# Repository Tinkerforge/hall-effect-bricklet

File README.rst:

Hall Effect Bricklet
====================

This repository contains the firmware source code and the hardware design
files. The documentation generator configs can be found at
https://github.com/Tinkerforge/generators

Repository Content
------------------

software/:
 * examples/: Examples for all supported languages
 * build/: Compiled files
 * src/: Source code of firmware
 * Makefile: Makefile to build project

hardware/:
 * Contains KiCad project files and additionally schematics as PDF

datasheets/:
 * Contains datasheets for sensors and complex ICs that are used

Hardware
--------

The hardware is designed with the open source EDA Suite KiCad
(http://www.kicad.org). Before you are able to open the files,
you have to install the Tinkerforge kicad-libraries
(https://github.com/Tinkerforge/kicad-libraries). You can either clone
them directly in hardware/ or clone them in a separate folder and
symlink them into hardware/
(ln -s kicad_path/kicad-libraries project_path/hardware). After that you
can open the .pro file in hardware/ with KiCad and from there view and
modify the schematics and the PCB layout.

Software
--------

If you want to do your own Brick/Bricklet firmware development we highly
recommend that you use our build environment setup script and read the
tutorial (https://www.tinkerforge.com/en/doc/Tutorials/Tutorial_Build_Environment/Tutorial.html).

To compile the C code we recommend you to install the newest GNU Arm Embedded
Toolchain (https://launchpad.net/gcc-arm-embedded/+download).
You also need to install bricklib (https://github.com/Tinkerforge/bricklib)
and brickletlib (https://github.com/Tinkerforge/brickletlib).

You can either clone it directly in software/src/ or clone it in a
separate folder and symlink it into software/src/
(ln -s bricklib_path/bricklib project_path/software/src/ and
ln -s brickletlib_path/brickletlib project_path/software/src/).
Finally make sure to have CMake installed
(http://www.cmake.org/cmake/resources/software.html).

After that you can build the firmware by invoking make in software/.
The firmware (.bin) can then be found in software/build/ and uploaded
with brickv (click button "Flashing" on start screen).

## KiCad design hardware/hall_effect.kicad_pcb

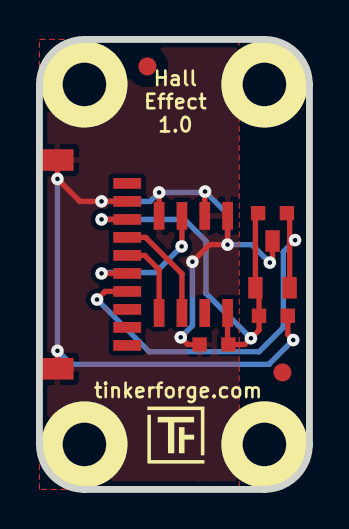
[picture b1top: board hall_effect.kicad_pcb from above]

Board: 2 copper layers, 15.0 x 25.0 mm, 14 parts (0 on the bottom side), 6 nets.

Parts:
C1, C2: 100nF; C0603
Fiducial_Mark: VAL**; Fiducial_Mark
Fiducial_Mark#2: VAL**; Fiducial_Mark
P1: CON-SENSOR
R1: 10k; R0603
U1: M24C64; SOIC8
U2: AH180N-W; SC59
U3, U4, U5, U6: DRILL; DRILL_NP
VAL: WEEE_7mm
VAL#2: CE_5mm

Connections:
GND: C1.2, C2.2, P1.2, P1.EP, U1.1, U1.2, U1.4, U2.2
unnamed: P1.4, U1.6
unnamed: P1.5, U1.5
unnamed: P1.6, U1.3
unnamed: P1.7, R1.2, U2.3
VCC: C1.1, C2.1, P1.3, R1.1, U1.8, U2.1

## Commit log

2013-08-09 Initial commit of Hall Effect Bricklet
2013-08-21 windows: Don't trigger a build in generate_makefile.bat
    Also use normal make instead of a special named one.
2013-08-27 Fix invalid parameter check
2013-09-13 Only send callback if value changed
2013-09-13 Add variable to save last edge count to BC
2013-09-13 Add examples for Hall Effect Bricklet
2013-09-20 Save current value compare it for edge callback
2013-09-20 Fix typo
2013-09-20 c: Avoid unused parameter warning
2013-10-15 add hardware files
2013-10-15 add license file
2013-10-18 Fix name to fit naming standard
2013-11-22 Change initial value to avoid detecting a phantom edge
2014-01-06 Add static assert for BrickContext size
2014-01-10 Add Perl examples
2014-01-15 php: Use const for constant values
2014-02-07 Add Mathematica examples
2014-02-10 perl: fixed namespace
2014-02-12 javascript: add examples
2014-02-18 javascript: examples fixed
2014-02-20 javascript: add html examples
2014-02-24 javascript: port 4280, startExample()
2014-02-28 javascript: Break long lines and cleanup whitespace
2014-03-05 Add LabVIEW examples
2014-03-06 labview: Add examples in LV2010 format
2014-03-25 matlab: add examples
2014-04-02 java: Unify constants style
2014-04-02 perl: Unify print style
2014-04-17 matlab: Adapt examples to new callback style
2014-04-17 matlab: Add parentheses to make pygments happy
2014-07-15 java: Replace System.console() usage with an Eclipse compatible pattern
2014-12-02 Use ReadLine instead of ReadKey for C# example
2015-02-13 vbnet: Use ReadLine instead of ReadKey
    Because ReadKey doesn't work with a pipe as stdin on the RED Brick.
2015-03-02 windows: Stop cmake from searching for mingw32-make.exe
    Using MinGW Makefiles as generator makes cmake search for mingw32-make.exe
    which might not be installed because GnuWin32's make.exe is used instead.
2015-04-09 c: Whitespace
2015-06-18 Break long lines in Delphi example
2015-06-24 javascript: Clean up output creation
2015-06-29 octave: Handle long difference between Octave 3.6 and 3.8
    In Octave 3.6 a long is not automatically handled as a number.
2015-07-23 Make JavaScript browser example textarea readonly
2015-07-27 Cleanup C/C++, C#, Java and Python examples
2015-07-29 Reformat changelog
2015-08-07 Use full device class name in Python examples
2015-08-07 Unify comments in C/C++, C#, Python and Ruby examples
2015-08-12 Fix minor warnings in C/C++ examples
2015-08-14 Cleanup Delphi example
2015-08-18 Cleanup VB.NET example
2015-08-19 Cleanup Perl examples
2015-09-09 Duplicate cmake call to fix bug during cmake creation
2015-09-30 Generator based example cleanup
2015-11-12 matlab: Fix callback handling for R2014a
    http://undocumentedmatlab.com/blog/matlab-callbacks-for-java-events-in-r2014a
2015-11-25 Include date and commit into changelog
2015-11-30 vbnet: Break long line
2016-05-18 c: Add missing device destroy call
2016-06-29 Whitespace
2016-07-01 Make the change UID comment more explicit
2017-04-13 csharp: Adapt example
2017-06-02 octave: Use javaObject instead of deprecated java_new
2017-07-31 Add 3d information (final)
2017-07-31 Add 3d information; fix EdgeCuts
2017-07-31 Add 3d model (*.FCStd & *.step)
2017-11-30 Update examples from generator
2017-12-07 mathematica: Also generate .nb files
2018-01-26 c: Fine-tune printf format
2018-02-02 c: Update example
2018-02-19 javascript: Close div tag correctly
2018-02-20 Cleanup KiCad libraries config
    Ensure LibDir=kicad-libraries and LibName1=tinkerforge.
    Remove special library.
2018-05-24 perl: Use strict in examples
2018-07-11 Add Makefile with docker support
2018-07-11 Remove obsolete generate_makefile scripts
2018-07-11 Update directory structure and build instructions
2018-10-30 Fix parameter names in examples
2018-11-06 Add rust examples
2018-11-07 rust: Accept host names for ip connection, fix naming inconsistencies
2018-11-07 rust: Rename callback receivers.
2018-12-14 Add go examples.
2018-12-18 go: Change import path.
2018-12-18 go: Change import path again.
2018-12-20 rust: Reformat examples.
2019-01-24 mqtt: Add examples.
2019-01-24 mqtt: Fix example header.
2019-01-24 mqtt: Remove executable bit in example permissions.
2019-01-24 go: Minor example fixes.
2019-01-24 mqtt: Minor example fixes.
2019-03-25 mqtt: Fix example whitespace.
2019-03-28 mqtt: Fix whitespace.
2019-08-22 c: Adapt to bindings changes
2020-01-13 examples: Use python3 input instead of python2 raw_input.
2020-01-13 examples: mqtt: Remove trailing whitespace.
2021-10-25 Update KiCad link
    https://www.kicad.org/blog/2021/10/Avoid-links-to-former-kicad-domain/
2022-05-10 go: Fix format string
2022-07-06 Add license files.

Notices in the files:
hardware/hall_effect.kicad_pcb:
Licensed under CERN OHL v.1.1
Copyright (©) 2013, B.Nordmeyer
Copyright Tinkerforge GmbH 2013.
This documentation describes Open Hardware and is licensed under the
CERN OHL v. 1.1.
